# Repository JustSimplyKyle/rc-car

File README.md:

# Project Description
## tl;dr
a esp-32 powered rc-car, with a step-motor serving as its primary transmission force, using belt wheels for synchronzied left-right wheel, utilizing a mg996r for turning curcuits, displaying all infos on a 128x64 oled display, finally using 3d-printed parts for the car assembly

the pcb is designed using KiCad, while we use Rhino for 3d modeling software.
## why
our school hosted a simple car competition, a really simple one where there's just TT-motors wired to a wireless controller.
my friend and i had so much issues with that car, that we decided we want to make a new-and-improved:tm: version of it!
## wiring diagarm
## screenshots
|  |  |
| :---: | :---: |
| *(pcb layout)* | *(3d view)* |

| Image | Description |
| :---: | :--- |
|  | *(schematic)* |

# Project Structure
the root of the project contains the setup of the firmware, written in esp32-rust.
- `src/bin` - the actual production code for the esp32
- `src/motor` - all the motor control codes are extraplated in here, with mostly complete compile time checking so that timer usage aren't checked at runtime
- `src/ps2.rs & src/ps2_controller_task.rs` - the controller reception api
- `setup` - the pcb & schemcatic(kicad)
- `3d_models` - the 3d models

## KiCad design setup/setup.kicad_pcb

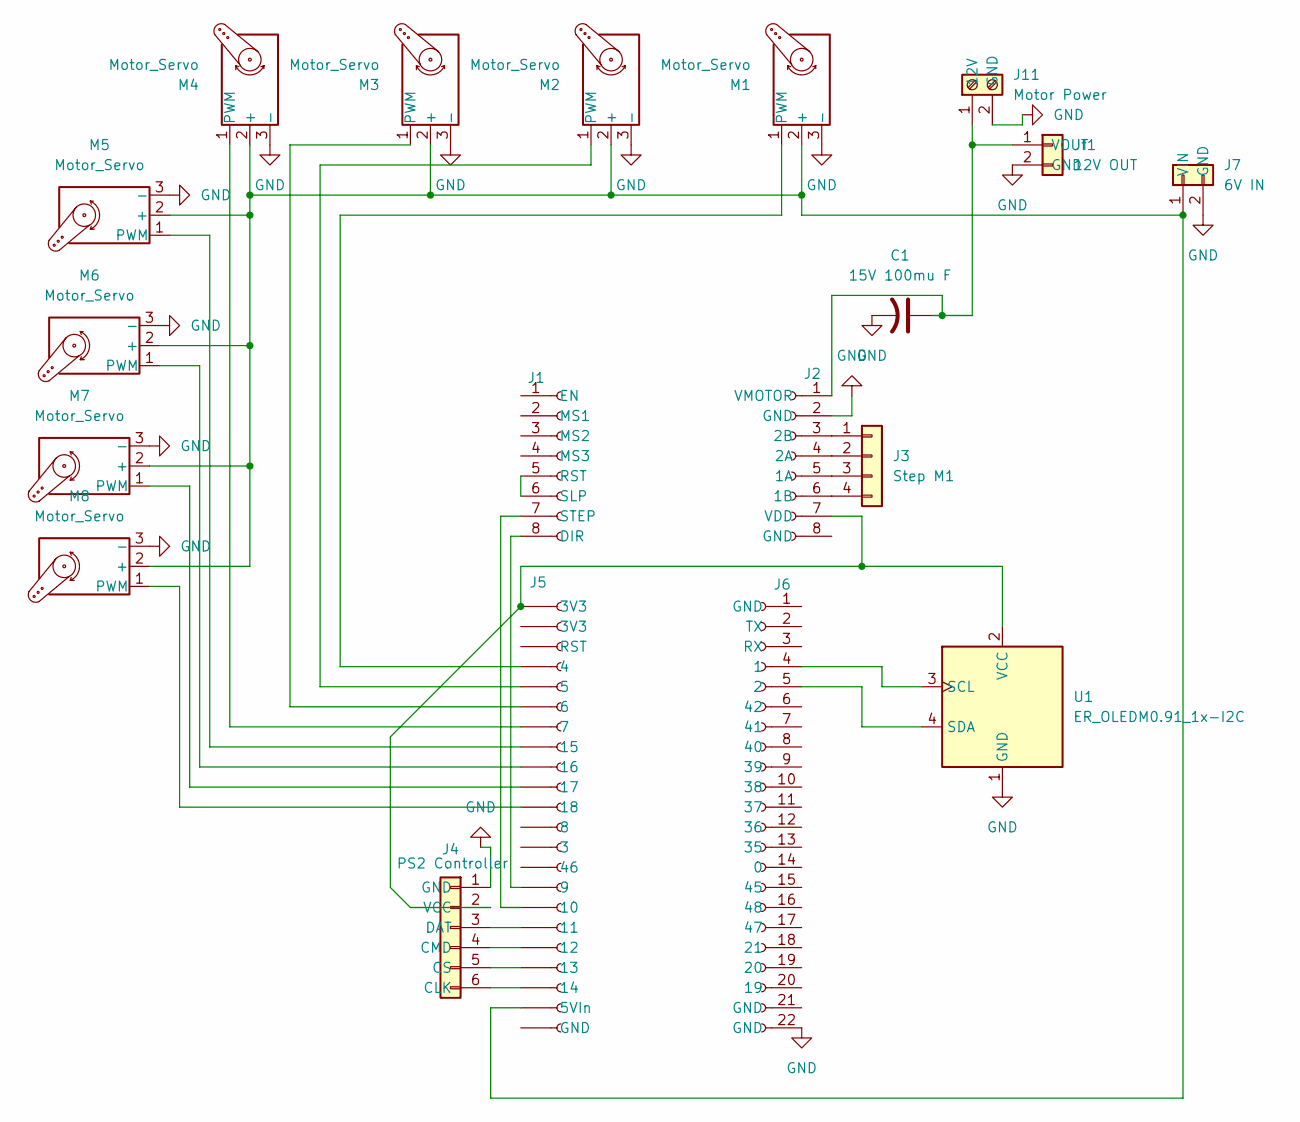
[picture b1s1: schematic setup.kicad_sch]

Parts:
C1: 15V 100mu F; C_Radial_D10.0mm_H12.5mm_P5.00mm
J1, J2: Conn_01x08_Socket; PinSocket_1x08_P2.54mm_Vertical
J3: Step M1; JST_PH_B4B-PH-K_1x04_P2.00mm_Vertical
J4: PS2 Controller; JST_PH_B6B-PH-K_1x06_P2.00mm_Vertical
J5, J6: Conn_01x22_Socket; PinSocket_1x22_P2.54mm_Vertical
J7: 6V IN; JST_VH_B2P-VH-FB-B_1x02_P3.96mm_Vertical
J11: Motor Power; JST_VH_B2P-VH-FB-B_1x02_P3.96mm_Vertical
Jf1: 12V OUT; JST_VH_B2P-VH-FB-B_1x02_P3.96mm_Vertical
M1, M2, M3, M4, M5, M6, M7, M8: Motor_Servo; JST_PH_B3B-PH-K_1x03_P2.00mm_Vertical
U1: ER_OLEDM0.91_1x-I2C; JST_XH_S4B-XH-A-1_1x04_P2.50mm_Horizontal

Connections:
GND: C1.2, J2.2 (GND), J4.1 (GND), J6.22 (GND), J7.2 (GND), J11.2 (GND), Jf1.2 (GND), M1.3 (-), M2.3 (-), M3.3 (-), M4.3 (-), M5.3 (-), M6.3 (-), M7.3 (-), M8.3 (-), U1.1 (GND)
unnamed: J1.8 (DIR), J5.15 (9)
unnamed: J1.5 (RST), J1.6 (SLP)
unnamed: J1.7 (STEP), J5.16 (10)
unnamed: J2.5 (1A), J3.3
unnamed: J2.6 (1B), J3.4
unnamed: J2.4 (2A), J3.2
unnamed: J2.3 (2B), J3.1
unnamed: J2.7 (VDD), J4.2 (VCC), J5.1 (3V3), U1.2 (VCC)
unnamed: J4.6 (CLK), J5.20 (14)
unnamed: J4.4 (CMD), J5.18 (12)
unnamed: J4.5 (CS), J5.19 (13)
unnamed: J4.3 (DAT), J5.17 (11)
unnamed: J5.21 (5VIn), J7.1 (VIN), M1.2 (+), M2.2 (+), M3.2 (+), M4.2 (+), M5.2 (+), M6.2 (+), M7.2 (+), M8.2 (+)
unnamed: J5.8 (15), M5.1 (PWM)
unnamed: J5.9 (16), M6.1 (PWM)
unnamed: J5.10 (17), M7.1 (PWM)
unnamed: J5.11 (18), M8.1 (PWM)
unnamed: J6.4 (1), U1.3 (SCL)
unnamed: J6.5 (2), U1.4 (SDA)
unnamed: C1.1, J2.1 (VMOTOR), J11.1 (12V), Jf1.1 (VOUT)
unnamed: J5.4, M1.1 (PWM)
unnamed: J5.5, M2.1 (PWM)
unnamed: J5.6, M3.1 (PWM)
unnamed: J5.7, M4.1 (PWM)

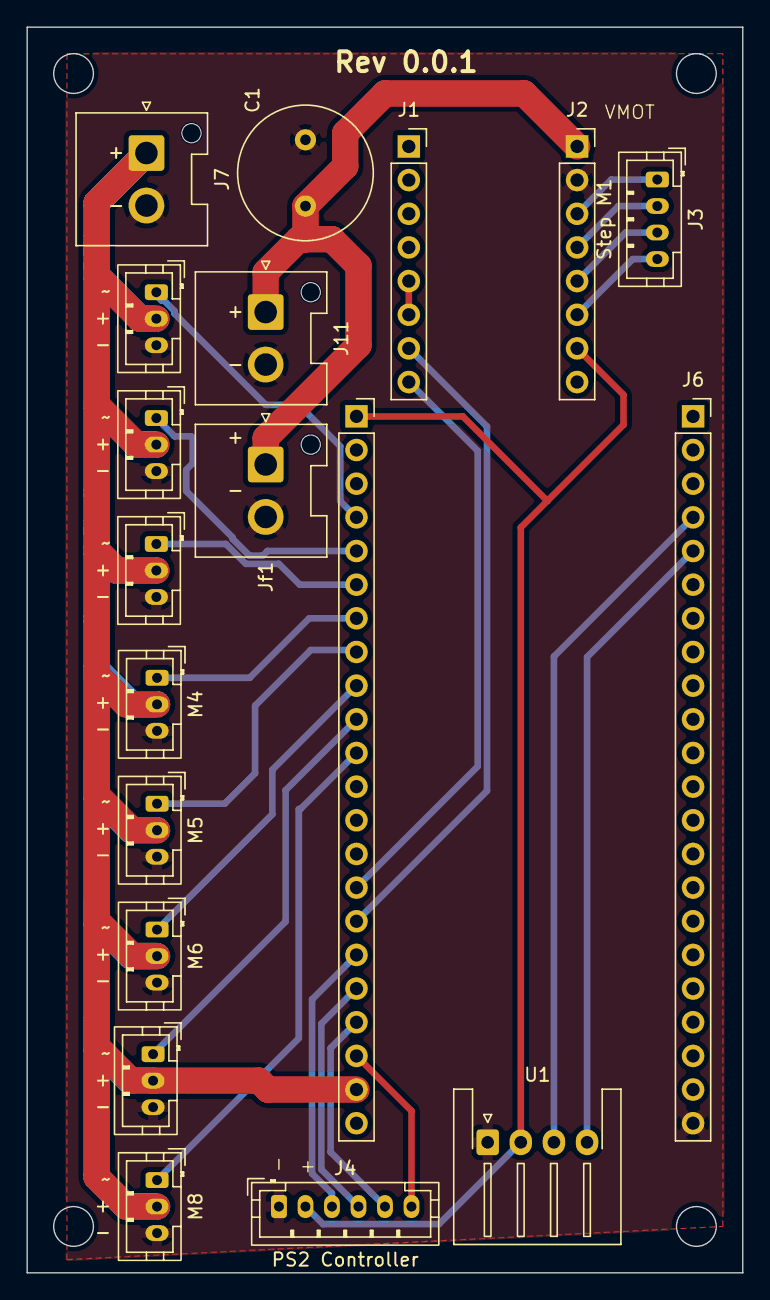
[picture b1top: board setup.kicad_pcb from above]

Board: 4 copper layers, 54.0 x 94.0 mm, 19 parts (0 on the bottom side), 25 nets.

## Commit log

2026-03-31 feat: initial commit
2026-04-01 feat: ledc except mcpwm
2026-04-05 feat: cleanup
2026-04-05 feat: eros inspired timer based container
2026-04-21 feat: step motor
2026-04-22 feat: include pcb
2026-04-23 feat: add oled(pcb)
2026-04-23 feat: separate step motor into module
2026-04-23 feat: re-order pcb
2026-04-23 feat: swap below upper
2026-04-23 feat: use two-layer routing for motor voltages
2026-04-23 feat: attempt to add copper fill for servo vins
2026-04-23 fix: route gnd
2026-04-23 feat: make board jlcpcb compatiable
2026-04-25 feat: add jlcpcb & fix vh connection
2026-04-26 feat: readme!
2026-04-26 fix: introduce `-`
2026-04-27 feat: make ledc motor accsept servo too
2026-05-08 feat: make direction switchig in step motor possible
2026-05-09 feat: make dc-motor multi-variable control
2026-05-10 feat: make dc_motor actually work
2026-05-10 refactor: refactor so that ledc and mcpwm have proper structure
2026-05-11 feat: better channel storage
2026-05-12 feat: add servo & display
2026-05-12 refactor: make `PwmMotor` control angles too
2026-05-12 feat: move i2c bus oled into second core
2026-05-13 fix: make initial angle clamp to min and max
2026-05-14 feat: make controls more sane
2026-05-17 feat: use uart instead of espnow
